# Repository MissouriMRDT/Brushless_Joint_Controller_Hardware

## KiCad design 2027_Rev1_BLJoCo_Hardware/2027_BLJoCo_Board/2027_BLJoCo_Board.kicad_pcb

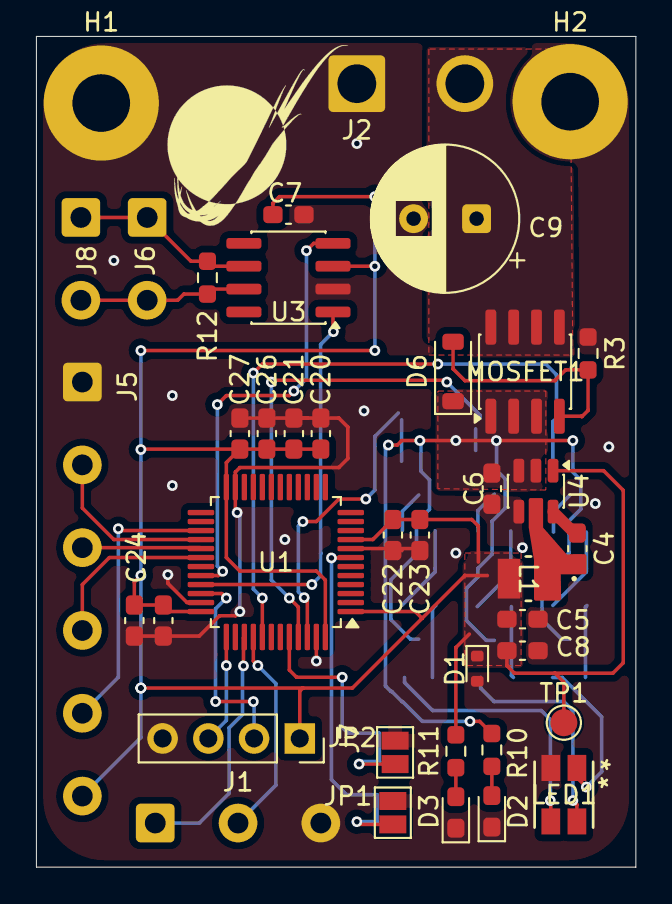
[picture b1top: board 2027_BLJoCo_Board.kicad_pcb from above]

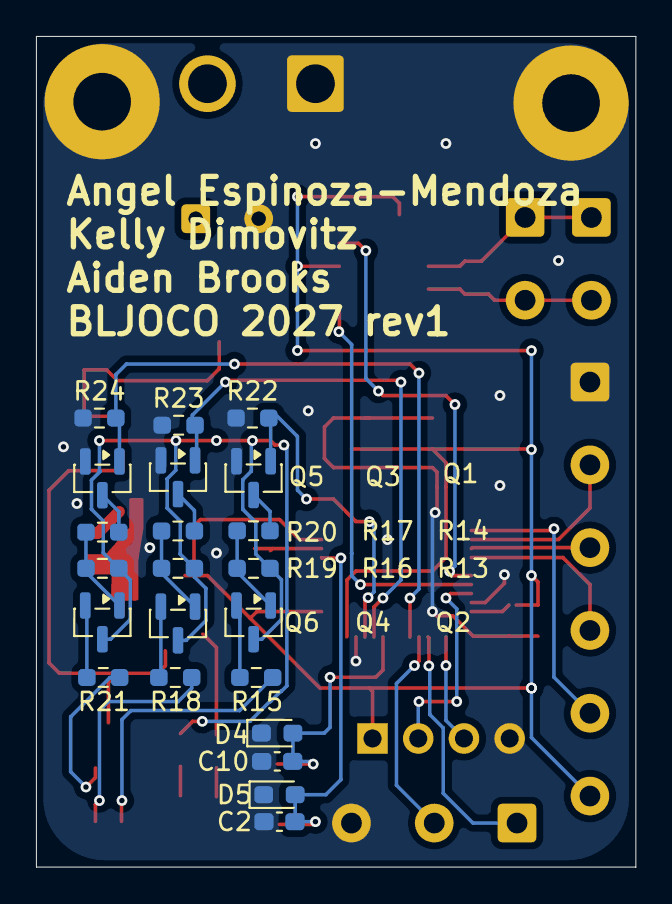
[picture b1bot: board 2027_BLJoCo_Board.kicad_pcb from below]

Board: 2 copper layers, 33.3 x 46.1 mm, 61 parts (22 on the bottom side), 38 nets.

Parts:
C2, C4, C7, C10, C21, C25, C26, C27: 100nF; C_0603_1608Metric_Pad1.08x0.95mm_HandSolder
C5, C8: 22uF; C_0603_1608Metric_Pad1.08x0.95mm_HandSolder
C6: 10uF; C_0603_1608Metric_Pad1.08x0.95mm_HandSolder
C9: 100uf; CP_Radial_D8.0mm_P3.50mm
C20, C24: 4.7uF; C_0603_1608Metric_Pad1.08x0.95mm_HandSolder
C22: 10nF; C_0603_1608Metric_Pad1.08x0.95mm_HandSolder
C23: 1uF; C_0603_1608Metric_Pad1.08x0.95mm_HandSolder
D1: MMSZ4685-TP; D_SOD-523
D2, D3: GREEN; LED_0603_1608Metric_Pad1.05x0.95mm_HandSolder
D4, D5: D_TVS; D_0603_1608Metric_Pad1.05x0.95mm_HandSolder
D6: MMSZ5240BT1G; D_SOD-123
H1, H2: MountingHole_Pad; MountingHole_3.2mm_M3_Pad
J1: Conn_01x03; SolderWire-0.5sqmm_1x03_P4.6mm_D0.9mm_OD2.1mm
J2: Conn_01x02; SolderWire-1.5sqmm_1x02_P6mm_D1.7mm_OD3mm
J5: Conn_01x06; SolderWire-0.5sqmm_1x06_P4.6mm_D0.9mm_OD2.1mm
J6, J8: Conn_01x02; SolderWire-0.5sqmm_1x02_P4.6mm_D0.9mm_OD2.1mm
J7: Conn_01x04; PinSocket_1x04_P2.54mm_Vertical
JP1, JP2: Jumper_2_Open; SolderJumper-2_P1.3mm_Open_Pad1.0x1.5mm
L1: 3.9uH; IND_TFM252012ALMA1R0MTAA_TDK
LED1: XZM2CRKM2DGFBB45SCCB; PLCC4_3p5x2p8_SLD
MOSFET1: TPC8132_LQS; SOIC-8_3.9x4.9mm_P1.27mm
Q1, Q3, Q5: BSS138; SOT-23
Q2, Q4, Q6: AO3401A; SOT-23
R3, R22, R23, R24: 1k; R_0603_1608Metric_Pad0.98x0.95mm_HandSolder
R10: 5.5k; R_0603_1608Metric_Pad0.98x0.95mm_HandSolder
R11: 330; R_0603_1608Metric_Pad0.98x0.95mm_HandSolder
R12: 120; R_0603_1608Metric_Pad0.98x0.95mm_HandSolder
R13, R16, R19: 5k; R_0603_1608Metric_Pad0.98x0.95mm_HandSolder
R14, R17, R20: 10k; R_0603_1608Metric_Pad0.98x0.95mm_HandSolder
R15, R18: 820; R_0603_1608Metric_Pad0.98x0.95mm_HandSolder
R21: 510; R_0603_1608Metric_Pad0.98x0.95mm_HandSolder
TP1: TestPoint; TestPoint_Pad_D1.5mm
U1: STM32F072C8Tx; LQFP-48_7x7mm_P0.5mm
U3: SN65HVD232; SOIC-8_3.9x4.9mm_P1.27mm
U4: AP63203WU; TSOT-23-6

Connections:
+3.3V: C5.1, C7.1, C8.1, C20.1, C21.1, C22.1, C23.1, C24.1, C25.1, C26.1, C27.1, D1.1 (K), J5.6, J7.1, L1.2, R11.1, TP1.1 (1_1), U1.1 (VBAT), U1.9 (VDDA), U1.24 (VDD), U1.48 (VDD), U3.3 (VCC), U4.1 (FB)
+24V: C6.1, D6.1, MOSFET1.1 (S), MOSFET1.2, MOSFET1.3, Q2.3 (D), Q4.3 (D), Q6.3 (D), R10.1, R13.1, R16.1, R19.1, U4.2 (EN), U4.3 (IN)
/CAN RX: U1.32 (PA11), U3.4 (R)
/CAN TX: U1.33 (PA12), U3.1 (D)
/CANH: J6.2, J8.2, R12.1, U3.7 (CANH)
/CANL: J6.1, J8.1, R12.2, U3.6 (CANL)
/ENC A: J5.4, U1.30 (PA9)
/ENC B: J5.3, U1.29 (PA8)
/ENC I: J5.2, U1.28 (PB15)
/ENC_ABS: J5.5, U1.27 (PB14)
/LIM A: J1.1, U1.39 (PB3)
/LIM B: J1.2, U1.40 (PB4)
/SWDCLK: J7.2, U1.34 (PA13)
/SWDIO: J7.3, U1.37 (PA14)
/boot: C10.1, D4.2 (A2), JP2.2 (B), U1.44 (BOOT0)
/nrst: C2.1, D5.2 (A2), JP1.2 (B), U1.7 (NRST)
GND: C2.2, C5.2, C6.2, C7.2, C8.2, C9.2, C10.2, C20.2, C21.2, C22.2, C23.2, C24.2, C25.2, C26.2, C27.2, D1.2 (A), D2.1 (K), D3.1 (K), D4.1 (A1), D5.1 (A1), H1.1 (1_1), H2.1 (1_1), J1.3, J2.1, J5.1, J7.4, JP1.1 (A), JP2.1 (A), LED1.4, Q1.2 (S), Q3.2 (S), Q5.2 (S), R3.2, R22.2, R23.2, R24.2, U1.8 (VSSA), U1.23 (VSS), U1.35 (VSS), U1.47 (VSS), U3.2 (GND), U4.4 (GND)
LED_B: R22.1, U1.46 (PB9)
LED_G: R23.1, U1.45 (PB8)
LED_R: R24.1, U1.41 (PB5)
unnamed: D2.2 (A), R10.2
unnamed: D3.2 (A), R11.2
unnamed: D6.2, MOSFET1.4 (G), R3.1
unnamed: Q1.3 (D), R14.2
unnamed: Q2.1 (G), R13.2, R14.1
unnamed: Q2.2 (S), R15.1
unnamed: Q3.3 (D), R17.2
unnamed: Q4.1 (G), R16.2, R17.1
unnamed: Q4.2 (S), R18.1
unnamed: Q5.3 (D), R20.2
unnamed: Q6.1 (G), R19.2, R20.1
unnamed: Q6.2 (S), R21.1
unnamed: C4.2, U4.6 (BST)
unnamed: C4.1, L1.1, U4.5 (SW)
V_AUX: C9.1, J2.2, MOSFET1.5 (D), MOSFET1.6, MOSFET1.7, MOSFET1.8
led_B_Out: LED1.3, R15.2
led_G_Out: LED1.2, R18.2
led_R_Out: LED1.1, R21.2
